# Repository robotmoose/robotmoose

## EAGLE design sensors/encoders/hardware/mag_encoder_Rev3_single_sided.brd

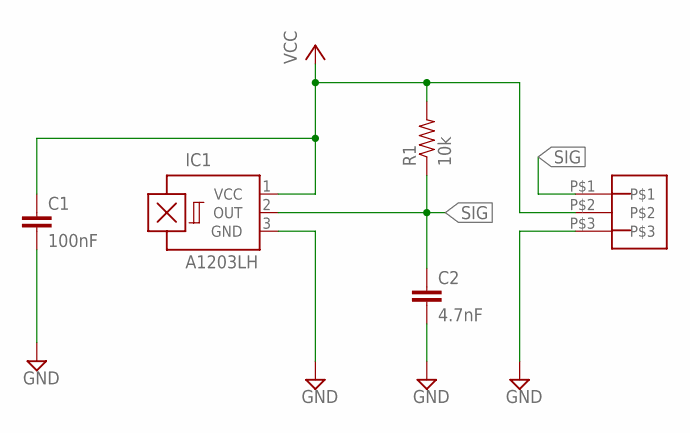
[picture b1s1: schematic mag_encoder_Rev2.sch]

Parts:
C1: 100nF; 0603-CAP
C2: 4.7nF; 0603-CAP
IC1: A1203LH; SOT23-W
R1: 10k; 0603
U$1: 3_PIN_JST-XH

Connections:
GND: C1.2, C2.2, IC1.3 (GND), U$1.P$3
SIG: C2.1, IC1.2 (OUT), R1.1, U$1.P$1
VCC: C1.1, IC1.1 (VCC), R1.2, U$1.P$2

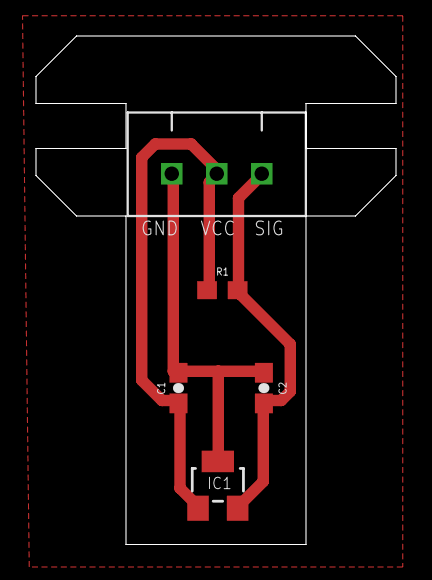
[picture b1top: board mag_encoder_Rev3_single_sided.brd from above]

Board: 1 copper layer, 20.0 x 28.2 mm, 5 parts (0 on the bottom side), 3 nets.

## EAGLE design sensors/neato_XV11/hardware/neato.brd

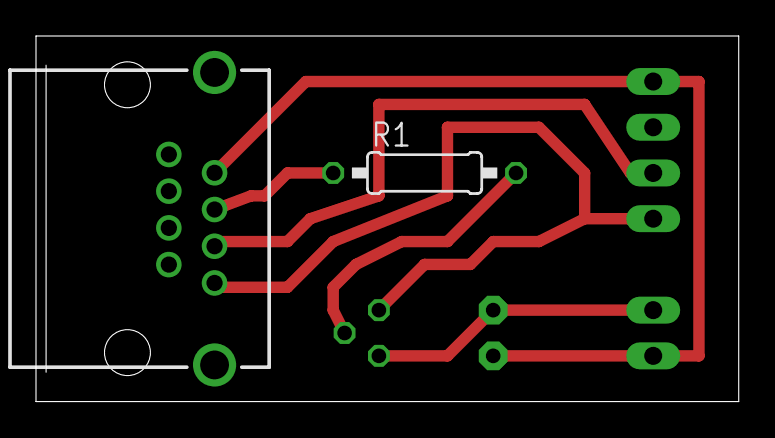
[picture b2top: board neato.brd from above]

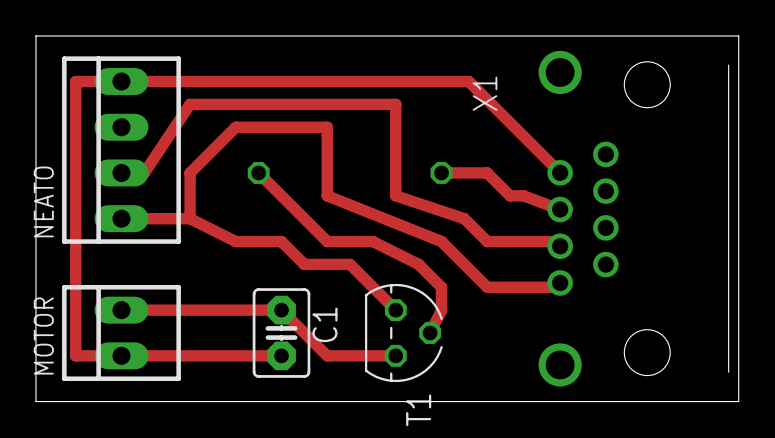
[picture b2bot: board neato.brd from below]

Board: 1 copper layer, 39.0 x 20.3 mm, 6 parts (5 on the bottom side), 6 nets.

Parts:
C1: C2.5-3
MOTOR: 22-23-2021
NEATO: 22-23-2041
R1: 0207/10
T1: 2N3904; TO92
X1: GLX-S-88M

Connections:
GND: NEATO.1, T1.3, X1.8
unnamed: C1.1, MOTOR.2, T1.1
unnamed: R1.1, X1.4
unnamed: NEATO.2, X1.6
unnamed: R1.2, T1.2
PWR: C1.2, MOTOR.1, NEATO.4, X1.2

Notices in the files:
parts and their libraries:
SparkFun-Capacitors: Licensing: Creative Commons ShareAlike 4.0 International - https://creativecommons.org/licenses/by-sa/4.0
